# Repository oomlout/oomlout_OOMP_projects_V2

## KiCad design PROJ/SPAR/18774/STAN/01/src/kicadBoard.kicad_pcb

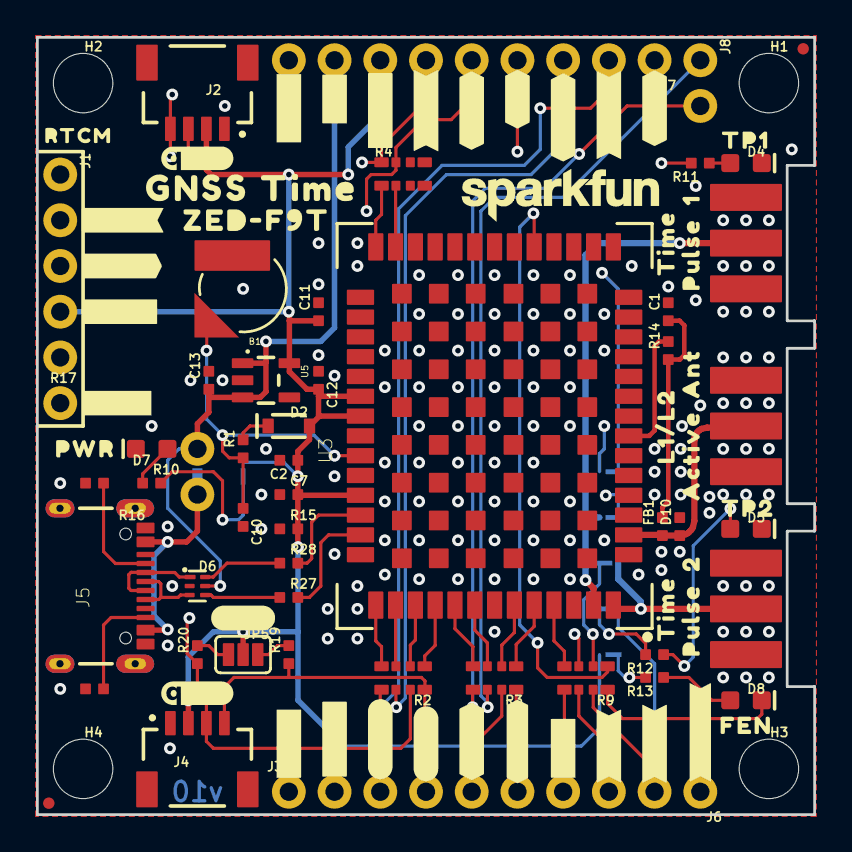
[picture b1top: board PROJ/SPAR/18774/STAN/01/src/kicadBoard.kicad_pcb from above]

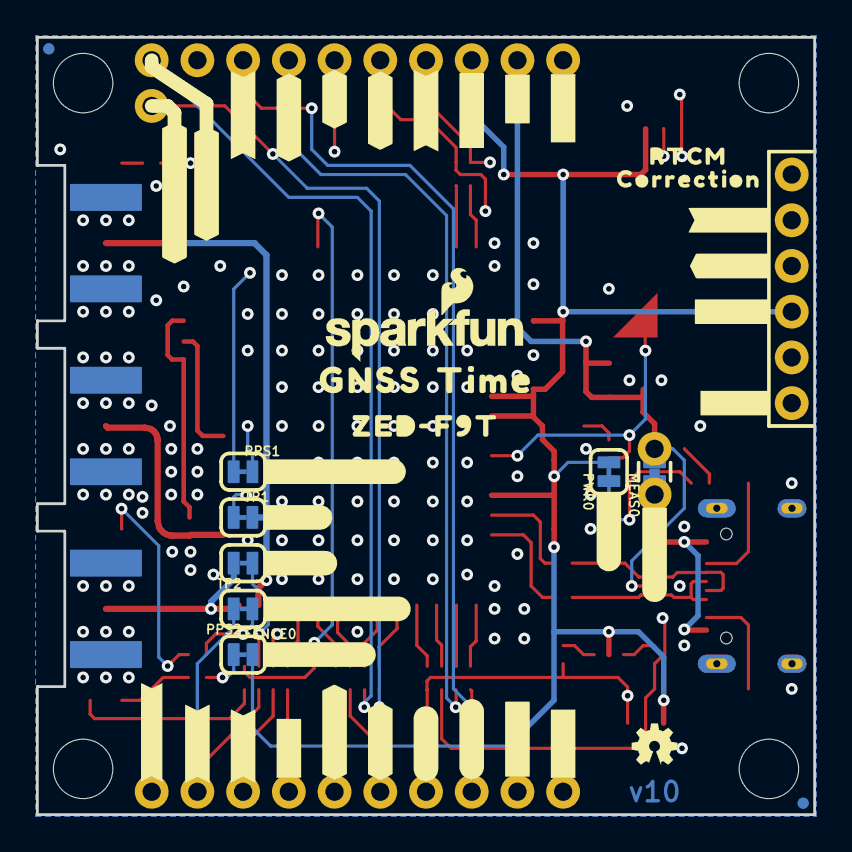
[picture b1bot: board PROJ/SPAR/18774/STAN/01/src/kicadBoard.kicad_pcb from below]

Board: 4 copper layers, 43.2 x 43.2 mm, 146 parts (47 on the bottom side), 57 nets.

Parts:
B1: 6.8MM_COIN_CELL; ML414H_IV01E
C1: 47pF; 0402-TIGHT
C2, C10, C11, C13: 1.0uF; 0402-TIGHT
C7, C12: 0.1uF; 0402-TIGHT
D2: 0.5A/40V/420mV; SOD-323
D4: YEL; LED-0603
D5: GRN; LED-0603
D6: PRTR5V0U2F; SOT886
D7: RED; LED-0603
D8: BLU; LED-0603
D10: PESD0402-0402T; 0402-TIGHT
E1, E2, E3: SMA; SMA-EDGE
FB1: 2.66Ω; 0402-TIGHT
FENCE0: JUMPER-SMT_2_NC_TRACE_SILK; SMT-JUMPER_2_NC_TRACE_SILK
FRAME2: FRAME-LEDGER; CREATIVE_COMMONS
H1, H2, H3, H4: STAND-OFF
J1: Radio; 1X06_NO_SILK
J2, J4: Qwiic Right Angle; JST04_1MM_RA
J3: PTH; 1X04_NO_SILK
J5: USB Female Type C Connector; USB-C-16P_4LAYER-PADS
J6: 1X06_NO_SILK
J7: 1X09_NO_SILK
J8: 1X02_NO_SILK
JP5: JUMPER-SMT_3_NO_SILK; SMT-JUMPER_3_NO_SILK
JP21, JP61, JP71, JP81: FIDUCIALUFIDUCIAL; FIDUCIAL-MICRO
LOGO1: OSHW-LOGOMINI; OSHW-LOGO-MINI
LOGO2: SFE_LOGO_NAME_FLAME.1_INCH; SFE_LOGO_NAME_FLAME_.1
LOGO3, LOGO4: QWIIC_LOGO_4MM; QWIIC_4MM
LOGO5: SFE_LOGO_NAME.1_INCH; SFE_LOGO_NAME_.1
MEAS0: JUMPER-COMBO_2_NC_TRACE; COMBO-JUMPER_2_NC_TRACE
PPS1, PPS2: JUMPER-SMT_2_NC_TRACE_SILK; SMT-JUMPER_2_NC_TRACE_SILK
PWR0: JUMPER-SMT_2_NC_TRACE_SILK; SMT-JUMPER_2_NC_TRACE_SILK
R1: 3.3K; 0402-TIGHT
R2, R3, R4, R9: 33; 1206_RA
R10, R11, R12, R13: 1k; 0402-TIGHT
R14: 10Ω; 0402-TIGHT
R15: 100k; 0402-TIGHT
R16, R17: 5.1k; 0402-TIGHT
R19, R20: 2.2k; 0402-TIGHT
R27, R28: 27OHM; 0402-TIGHT
TP1, TP2: JUMPER-SMT_2_NC_TRACE_SILK; SMT-JUMPER_2_NC_TRACE_SILK
U3: U-BLOX_ZED_F9T; ZED-F9X
U5: AP2112K-3.3V; SOT23-5
U$1, U$29, U$35, U$36, U$59, U$60: #3#3V#0
U$2: SPECIAL_INSTRUCTIONS-ORDERING; ORDERING_INSTRUCTIONS
U$3, U$28: #5V#1
U$4, U$27, U$38, U$39, U$61, U$62: #GND#2
U$5, U$8: ##CS##4
U$6: L1#L20
U$7, U$21: TIME0
U$9, U$10: #CIPO#6
U$11, U$12: #COPI#5
U$13: ACTIVE1
U$14, U$16: #RX2#1
U$15, U$37: ##RST##0
U$17, U$53: #SCL#3
U$18, U$22: #SDA#2
U$19, U$25: PULSE1
U$20: 12
U$23, U$24: #TX2#0
U$26: 20
U$30: #SCK#5
U$31: ANT1
U$32: #_TX2#0
U$33: #D_SEL#1
U$34, U$77: ZED#F9T0
U$40, U$70: GNSS0
U$41: ##SAFE##1
U$42, U$43: #INT#2
U$44, U$65: #FENCE#0
U$45: #TP2_LED#0
U$46, U$47: #TP1#3
U$48, U$49: #TP2#4
U$50: #TP2#0
U$51: #_FENCE#0
U$52: #TP1#0
U$54: #TP1_LED#0
U$55: #_RX2#0
U$56: PWR0
U$57: #PWR#0
U$58: #RX2_#0
U$63: TP10
U$64: TP21
U$66: #TX2_#0
U$67: #TX_RDY#0
U$68: #MEAS#0
U$69: #I�C#0
U$71, U$74: TIME1
U$72: ##SAFE##0
U$73: RTCM0
U$75: CORRECTION1
U$76: RTCM_0
U$78: FEN0

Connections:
3.3V: C2.1, C7.2, C11.1, C12.2, D2.A, FENCE0.2, J1.4, J2.2, J3.2, J4.2, J7.7, JP5.2, PWR0.2, R15.2, U3.33, U3.34, U3.38, U5.5
5V: C13.1, D6.5, J7.8, MEAS0.2, MEAS0.4, U5.1, U5.3
ANT_VCC: C1.1, FB1.2, R14.1
CC1: J5.A5, R17.2
CC2: J5.B5, R16.2
D+: D6.4, R27.1
D-: D6.6, R28.1
DSEL_LV: R3.P3, U3.47
D_SEL: J8.1, R3.P6
EXTINT: J6.4, R9.P5
EXTINT_LV: R9.P4, U3.51
FENCE_LV: R9.P1, U3.19
FENCE_STAT: D8.C, J6.1, R9.P8
GND: B1.-, C1.2, C2.2, C7.1, C10.2, C11.2, C12.1, C13.2, D4.C, D5.C, D6.2, D7.C, D10.2, E1.GND@0, E1.GND@1, E1.GND@2, E1.GND@3, E2.GND@0, E2.GND@1, E2.GND@2, E2.GND@3, E3.GND@0, E3.GND@1, E3.GND@2, E3.GND@3, J1.6, J2.1, J3.1, J4.1, J5.GND, J5.GND2, J7.9, R15.1, R16.1, R17.1, U3.1, U3.3, U3.12, U3.14, U3.32, U3.37, U3.41, U3.48, U3.G1, U3.G2, U3.G3, U3.G4, U3.G5, U3.G6, U3.G7, U3.G8, U3.G9, U3.G10, U3.G11, U3.G12, U3.G13, U3.G14, U3.G15, U3.G16, U3.G17, U3.G18, U3.G19, U3.G20, U3.G21, U3.G22, U3.G23, U3.G24, U3.G25, U3.G26, U3.G27, U3.G28, U3.G29, U3.G30, U3.G31, U3.G32, U3.G33, U3.G34, U3.G35, U3.G36, U3.G37, U3.G38, U3.G39, U3.G40, U3.G41, U3.G42, U3.G43, U3.G44, U3.G45, U3.G46, U3.G47, U3.G48, U5.2
GPS_ANT1: D10.1, E1.SIG, FB1.1, U3.2
unnamed: D4.A, R11.1
unnamed: PPS1.1, R11.2
unnamed: J5.VBUS1, J5.VBUS2, MEAS0.1, MEAS0.3
unnamed: R9.P3, TP1.1
unnamed: D2.C, R1.2
unnamed: R9.P2, TP2.1
unnamed: R27.2, U3.40
unnamed: R28.2, U3.39
unnamed: R14.2, U3.7
unnamed: D7.A, R10.1
unnamed: D5.A, R12.1
unnamed: PPS2.1, R12.2
unnamed: D8.A, R13.1
unnamed: FENCE0.1, R13.2
unnamed: PWR0.1, R10.2
unnamed: JP5.1, R20.2
unnamed: JP5.3, R19.2
PPS1_STAT: J6.3, PPS1.2, R9.P6
PPS2_STAT: J6.2, PPS2.2, R9.P7
RX1_LV: R2.P3, U3.43
RX2_LV: R4.P2, U3.26
RXI2: J1.3, J7.5, R4.P7
RXI/COPI: J7.3, R2.P6
SCL/SCK: J2.4, J3.4, J4.4, J7.1, R2.P8, R19.1
SCL_LV: R2.P1, U3.45
SDA/~CS: J2.3, J3.3, J4.3, J7.4, R2.P7, R20.1
SDA_LV: R2.P2, U3.44
TP1_LV: E2.SIG, TP1.2, U3.53
TP2_LV: E3.SIG, TP2.2, U3.54
TX1_LV: R2.P4, U3.42
TX2_LV: R4.P1, U3.27
TXO2: J1.2, J7.6, R4.P8
TXO/CIPO: J7.2, R2.P5
TX_READY: J8.2, R3.P5
TX_READY_LV: R3.P4, U3.46
UNP_D+: D6.3, J5.A6, J5.B6
UNP_D-: D6.1, J5.A7, J5.B7
V_BACKUP: B1.+, C10.1, R1.1, U3.36
~RESET: J6.6, R3.P7
~RESET_LV: R3.P2, U3.49
~SAFE: J6.5, R3.P8
~SAFE_LV: R3.P1, U3.50

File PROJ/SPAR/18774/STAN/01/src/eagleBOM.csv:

"Part";"Value";"Device";"Package";"Description";"DESIGNER";"PROD_ID";"REV";"VALUE";
"B1";"6.8MM_COIN_CELL";"ML414H_IV01E_BATTERY";"ML414H_IV01E";"SEIKO ML414H-IV01E Reflowable Lithium Battery";"";"BATT-14267";"";"";
"C1";"47pF";"47PF-0402_TIGHT-25V-5%-X7R";"0402-TIGHT";"47pF ceramic capacitors";"";"CAP-15063";"";"47pF";
"C2";"1.0uF";"1.0UF-0402T-16V-10%";"0402-TIGHT";"1µF ceramic capacitors";"";"CAP-12417";"";"1.0uF";
"C7";"0.1uF";"0.1UF-0402T-16V-10%";"0402-TIGHT";"0.1µF ceramic capacitors";"";"CAP-12416";"";"0.1uF";
"C10";"1.0uF";"1.0UF-0402T-16V-10%";"0402-TIGHT";"1µF ceramic capacitors";"";"CAP-12417";"";"1.0uF";
"C11";"1.0uF";"1.0UF-0402T-16V-10%";"0402-TIGHT";"1µF ceramic capacitors";"";"CAP-12417";"";"1.0uF";
"C12";"0.1uF";"0.1UF-0402T-6.3V-10%-X7R";"0402-TIGHT";"0.1µF ceramic capacitors";"";"CAP-14993";"";"0.1uF";
"C13";"1.0uF";"1.0UF-0402T-16V-10%";"0402-TIGHT";"1µF ceramic capacitors";"";"CAP-12417";"";"1.0uF";
"D2";"0.5A/40V/420mV";"DIODE-SCHOTTKY-PMEG4005EJ";"SOD-323";"Schottky diode";"";"DIO-10955";"";"0.5A/40V/420mV";
"D4";"YEL";"LED-YELLOW0603";"LED-0603";"Yellow SMD LED";"";"DIO-09003";"";"Yellow";
"D5";"GRN";"LED-GREEN0603";"LED-0603";"Green SMD LED";"";"DIO-00821";"";"GREEN";
"D6";"PRTR5V0U2F";"PRTR5V0U2F";"SOT886";"A small ESD protection device. Most commonly used on USB D+/D- signals to protect large, expensive, or especially sensitive USB enabled devices.";"";"DIO-14084";"";"";
"D7";"RED";"LED-RED0603";"LED-0603";"Red SMD LED";"";"DIO-00819";"";"RED";
"D8";"BLU";"LED-BLUE0603";"LED-0603";"Blue SMD LED";"";"DIO-08575";"";"BLUE";
"D10";"PESD0402-0402T";"PESD0402-0402T";"0402-TIGHT";"ESD protection diode";"";"DIO-15359";"";"";
"E1";"SMA";"ANTENNA-SMA-GROUNDEDEDGE_SMA";"SMA-EDGE";"SMA Antenna Connector w/ Ground";"";"CONN-08289";"";"";
"E2";"SMA";"ANTENNA-SMA-GROUNDEDEDGE_SMA";"SMA-EDGE";"SMA Antenna Connector w/ Ground";"";"CONN-08289";"";"";
"E3";"SMA";"ANTENNA-SMA-GROUNDEDEDGE_SMA";"SMA-EDGE";"SMA Antenna Connector w/ Ground";"";"CONN-08289";"";"";
"FB1";"2.66Ω";"FERRITE_BEAD-0402-2.66Ω-1GHZ";"0402-TIGHT";"Ferrite Bead (blocks, cores, rings, chokes, etc.)";"";"NDUC-15072";"";"2.66Ω";
"FENCE";"JUMPER-SMT_2_NC_TRACE_SILK";"JUMPER-SMT_2_NC_TRACE_SILK";"SMT-JUMPER_2_NC_TRACE_SILK";"Normally closed trace jumper";"";"";"";"";
"FRAME2";"FRAME-LEDGER";"FRAME-LEDGER";"CREATIVE_COMMONS";"Schematic Frame - Ledger";"";"";"";"";
"H1";"STAND-OFF";"STAND-OFF";"STAND-OFF";"Stand Off";"";"";"";"";
"H2";"STAND-OFF";"STAND-OFF";"STAND-OFF";"Stand Off";"";"";"";"";
"H3";"STAND-OFF";"STAND-OFF";"STAND-OFF";"Stand Off";"";"";"";"";
"H4";"STAND-OFF";"STAND-OFF";"STAND-OFF";"Stand Off";"";"";"";"";
"J1";"Radio";"6_PIN_SERIAL_TARGET_NO_SILK";"1X06_NO_SILK";"6-pin header connection for use with the "FTDI BASIC" pinout - TARGET SIDE.";"";"";"";"";
"J2";"Qwiic Right Angle";"I2C_STANDARDQWIIC";"JST04_1MM_RA";"SparkFun I2C Standard Pinout Header";"";"CONN-13694";"";"Qwiic Right Angle";
"J3";"PTH";"I2C_STANDARD_NO_SILK";"1X04_NO_SILK";"SparkFun I2C Standard Pinout Header";"";"";"";"";
"J4";"Qwiic Right Angle";"I2C_STANDARDQWIIC";"JST04_1MM_RA";"SparkFun I2C Standard Pinout Header";"";"CONN-13694";"";"Qwiic Right Angle";
"J5";"USB Female Type C Connector";"USB_C_4-LAYER_PADS";"USB-C-16P_4LAYER-PADS";"USB Type C 16Pin Connector";"";"CONN-14122";"";"";
"J6";"";"CONN_06NO_SILK_FEMALE_PTH";"1X06_NO_SILK";"Multi connection point. Often used as Generic Header-pin footprint for 0.1 inch spaced/style header connections";"";"CONN-08437";"";"";
"J7";"";"CONN_09NO_SILK";"1X09_NO_SILK";"Multi connection point. Often used as Generic Header-pin footprint for 0.1 inch spaced/style header connections";"";"";"";"";
"J8";"";"CONN_021X02_NO_SILK";"1X02_NO_SILK";"Multi connection point. Often used as Generic Header-pin footprint for 0.1 inch spaced/style header connections";"";"";"";"";
"JP5";"JUMPER-SMT_3_NO_SILK";"JUMPER-SMT_3_NO_SILK";"SMT-JUMPER_3_NO_SILK";"Normally open jumper";"";"";"";"";
"JP21";"FIDUCIALUFIDUCIAL";"FIDUCIALUFIDUCIAL";"FIDUCIAL-MICRO";"Fiducial Alignment Points";"";"";"";"";
"JP61";"FIDUCIALUFIDUCIAL";"FIDUCIALUFIDUCIAL";"FIDUCIAL-MICRO";"Fiducial Alignment Points";"";"";"";"";
"JP71";"FIDUCIALUFIDUCIAL";"FIDUCIALUFIDUCIAL";"FIDUCIAL-MICRO";"Fiducial Alignment Points";"";"";"";"";
"JP81";"FIDUCIALUFIDUCIAL";"FIDUCIALUFIDUCIAL";"FIDUCIAL-MICRO";"Fiducial Alignment Points";"";"";"";"";
"LOGO1";"OSHW-LOGOMINI";"OSHW-LOGOMINI";"OSHW-LOGO-MINI";"Open-Source Hardware (OSHW) Logo";"";"";"";"";
"LOGO2";"SFE_LOGO_NAME_FLAME.1_INCH";"SFE_LOGO_NAME_FLAME.1_INCH";"SFE_LOGO_NAME_FLAME_.1";"SparkFun Font Logo w/ Flame";"";"";"";"";
"LOGO4";"QWIIC_LOGO_4MM";"QWIIC_LOGO_4MM";"QWIIC_4MM";"Qwiic Logos for placement on schematic and PCB. The 5.5mm silk logo is best for placing next to Qwiic connector.";"";"";"";"";
"LOGO5";"SFE_LOGO_NAME.1_INCH";"SFE_LOGO_NAME.1_INCH";"SFE_LOGO_NAME_.1";"SparkFun Font Logo";"";"";"";"";
"MEAS";"JUMPER-COMBO_2_NC_TRACE";"JUMPER-COMBO_2_NC_TRACE";"COMBO-JUMPER_2_NC_TRACE";"";"";"";"";"";
"PPS1";"JUMPER-SMT_2_NC_TRACE_SILK";"JUMPER-SMT_2_NC_TRACE_SILK";"SMT-JUMPER_2_NC_TRACE_SILK";"Normally closed trace jumper";"";"";"";"";
"PPS2";"JUMPER-SMT_2_NC_TRACE_SILK";"JUMPER-SMT_2_NC_TRACE_SILK";"SMT-JUMPER_2_NC_TRACE_SILK";"Normally closed trace jumper";"";"";"";"";
"PWR";"JUMPER-SMT_2_NC_TRACE_SILK";"JUMPER-SMT_2_NC_TRACE_SILK";"SMT-JUMPER_2_NC_TRACE_SILK";"Normally closed trace jumper";"";"";"";"";
"R1";"3.3K";"3.3KOHM-0402T-1/16W-1%";"0402-TIGHT";"3.3kΩ resistor";"";"RES-15923";"";"";
"R2";"33";"33OHM_RA-1206-1/16W-5%";"1206_RA";"EXB-38V330JV";"";"RES-15081";"";"33";
"R3";"33";"33OHM_RA-1206-1/16W-5%";"1206_RA";"EXB-38V330JV";"";"RES-15081";"";"33";
"R4";"33";"33OHM_RA-1206-1/16W-5%";"1206_RA";"EXB-38V330JV";"";"RES-15081";"";"33";
"R9";"33";"33OHM_RA-1206-1/16W-5%";"1206_RA";"EXB-38V330JV";"";"RES-15081";"";"33";
"R10";"1k";"1KOHM-0402T-1/16W-1%";"0402-TIGHT";"1kΩ resistor";"";"RES-14342";"";"1k";
"R11";"1k";"1KOHM-0402T-1/16W-1%";"0402-TIGHT";"1kΩ resistor";"";"RES-14342";"";"1k";
"R12";"1k";"1KOHM-0402T-1/16W-1%";"0402-TIGHT";"1kΩ resistor";"";"RES-14342";"";"1k";
"R13";"1k";"1KOHM-0402T-1/16W-1%";"0402-TIGHT";"1kΩ resistor";"";"RES-14342";"";"1k";
"R14";"10Ω";"10OHM-0402-1/16W-5%";"0402-TIGHT";"10Ω resistor";"";"RES-16072";"";"10Ω";
"R15";"100k";"100KOHM-0402T-1/16W-1%";"0402-TIGHT";"100kΩ resistor";"";"RES-13495";"";"100k";
"R16";"5.1k";"5.1KOHM-0402T-1/16W-1%";"0402-TIGHT";"";"";"RES-14340";"";"5.1k";
"R17";"5.1k";"5.1KOHM-0402T-1/16W-1%";"0402-TIGHT";"";"";"RES-14340";"";"5.1k";
"R19";"2.2k";"2.2KOHM-0402T-1/16W-1%";"0402-TIGHT";"2.2kΩ resistor";"";"RES-14341";"";"2.2k";
"R20";"2.2k";"2.2KOHM-0402T-1/16W-1%";"0402-TIGHT";"2.2kΩ resistor";"";"RES-14341";"";"2.2k";
"R27";"27OHM";"27OHM";"0402-TIGHT";"27Ω resistor";"";"RES-15238";"";"";
"R28";"27OHM";"27OHM";"0402-TIGHT";"27Ω resistor";"";"RES-15238";"";"";
"TP1";"JUMPER-SMT_2_NC_TRACE_SILK";"JUMPER-SMT_2_NC_TRACE_SILK";"SMT-JUMPER_2_NC_TRACE_SILK";"Normally closed trace jumper";"";"";"";"";
"TP2";"JUMPER-SMT_2_NC_TRACE_SILK";"JUMPER-SMT_2_NC_TRACE_SILK";"SMT-JUMPER_2_NC_TRACE_SILK";"Normally closed trace jumper";"";"";"";"";
"U$2";"SPECIAL_INSTRUCTIONS-ORDERING";"SPECIAL_INSTRUCTIONS-ORDERING";"ORDERING_INSTRUCTIONS";"Special Ordering/Production Instructions Alert";"";"";"";"";
"U3";"U-BLOX_ZED_F9T";"U-BLOX_ZED_F9RT";"ZED-F9X";"u-blox ZED-F9T";"";"IC-16292";"";"";
"U5";"AP2112K-3.3V";"V_REG_AP2112K-3.3V";"SOT23-5";"AP2112 - 600mA CMOS LDO Regulator w/ Enable";"";"VREG-12457";"";"3.3V";

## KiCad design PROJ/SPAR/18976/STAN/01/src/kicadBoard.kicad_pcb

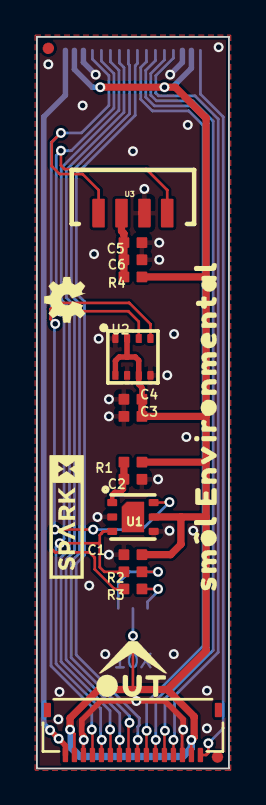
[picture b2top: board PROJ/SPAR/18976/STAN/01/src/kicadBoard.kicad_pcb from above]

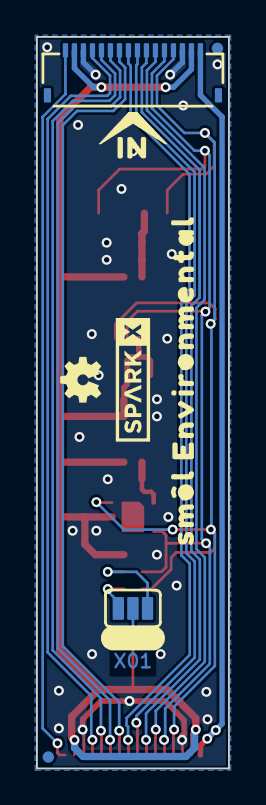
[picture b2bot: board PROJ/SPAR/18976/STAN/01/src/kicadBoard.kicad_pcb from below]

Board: 2 copper layers, 10.7 x 40.6 mm, 33 parts (10 on the bottom side), 18 nets.

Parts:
C1, C2: 1.0uF; 0402-TIGHT
C3, C5: 2.2uF; 0402-TIGHT
C4, C6: 0.1uF; 0402-TIGHT
FD1, FD2, FD3, FD4: FIDUCIALUFIDUCIAL; FIDUCIAL-MICRO
FRAME1: FRAME-LEDGER; CREATIVE_COMMONS
IN0: FPC_16_0.5MM
JP1: JUMPER-SMT_3_NO_SILK; SMT-JUMPER_3_NO_SILK
LOGO1: SPECIAL_INSTRUCTIONS-ORDERING; ORDERING_INSTRUCTIONS
LOGO2, LOGO3: OSHW-LOGOMINI; OSHW-LOGO-MINI
OUT0: FPC_16_0.5MM
R1, R4: 4.7; 0402-TIGHT
R2, R3: 4.7k; 0402-TIGHT
U1: SGP40
U2: BME280; LGA-8-2.5X2.5
U3: VEML7700-TT; VEML7700_TT
U$1, U$20: SPARKX-LOGO3; SPARKX-SMALL
U$2, U$4: SM�L_ENVIRONMENTAL0
U$3, U$9: SMOL_LOGOSMALL; SMOL_SMALL
U$5: #I�C#0
U$8: IN0
U$17: OUT0

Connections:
3.3V: C1.1, C3.1, C4.1, IN0.2, IN0.15, JP1.2, OUT0.2, OUT0.15, R1.2, R4.2, U1.5, U2.2, U2.6, U2.8
CIPO: IN0.6, OUT0.6
COPI: IN0.5, OUT0.5
CS0: IN0.7, OUT0.7
CS1: IN0.8, OUT0.8
CS2: IN0.9, OUT0.9
GND: C1.2, C2.2, C3.2, C4.2, C5.2, C6.2, IN0.3, IN0.14, OUT0.3, OUT0.14, U1.2, U1.4, U1.DIEPAD, U2.1, U2.5, U2.7, U3.3
GPIO0: IN0.10, OUT0.10
GPIO1: IN0.11, OUT0.11
unnamed: C2.1, R1.1, U1.1
unnamed: JP1.3, R2.2
unnamed: JP1.1, R3.2
unnamed: C5.1, C6.1, R4.1, U3.2
PROC_PWR_EN: IN0.1, OUT0.1
SCL: IN0.13, OUT0.13, R3.1, U1.6, U2.4, U3.1
SCLK: IN0.4, OUT0.4
SDA: IN0.12, OUT0.12, R2.1, U1.3, U2.3, U3.4
V_USB: IN0.16, OUT0.16

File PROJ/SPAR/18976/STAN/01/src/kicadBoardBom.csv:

"Id";"Designator";"Package";"Quantity";"Designation";"Supplier and ref";
1;"R1,R4";"0402-TIGHT";2;"4.7";;;
2;"R3,R2";"0402-TIGHT";2;"4.7k";;;
3;"C6,C4";"0402-TIGHT";2;"0.1uF";;;
4;"FD1,FD3,FD2,FD4";"FIDUCIAL-MICRO";4;"FIDUCIALUFIDUCIAL";;;
5;"U2";"LGA-8-2.5X2.5";1;"BME280";;;
6;"U$2,U$4";"SM�L_ENVIRONMENTAL0";2;"";;;
7;"U3";"VEML7700_TT";1;"VEML7700-TT";;;
8;"OUT0,IN0";"FPC_16_0.5MM";2;"";;;
9;"U$3,U$9";"SMOL_SMALL";2;"SMOL_LOGOSMALL";;;
10;"LOGO2,LOGO3";"OSHW-LOGO-MINI";2;"OSHW-LOGOMINI";;;
11;"U$1,U$20";"SPARKX-SMALL";2;"SPARKX-LOGO3";;;
12;"C3,C5";"0402-TIGHT";2;"2.2uF";;;
13;"C1,C2";"0402-TIGHT";2;"1.0uF";;;
14;"U1";"SGP40";1;"SGP40";;;
15;"LOGO1";"ORDERING_INSTRUCTIONS";1;"SPECIAL_INSTRUCTIONS-ORDERING";;;
16;"U$17";"OUT0";1;"";;;
17;"FRAME1";"CREATIVE_COMMONS";1;"FRAME-LEDGER";;;
18;"U$5";"#I�C#0";1;"";;;
19;"U$8";"IN0";1;"";;;
20;"JP1";"SMT-JUMPER_3_NO_SILK";1;"JUMPER-SMT_3_NO_SILK";;;

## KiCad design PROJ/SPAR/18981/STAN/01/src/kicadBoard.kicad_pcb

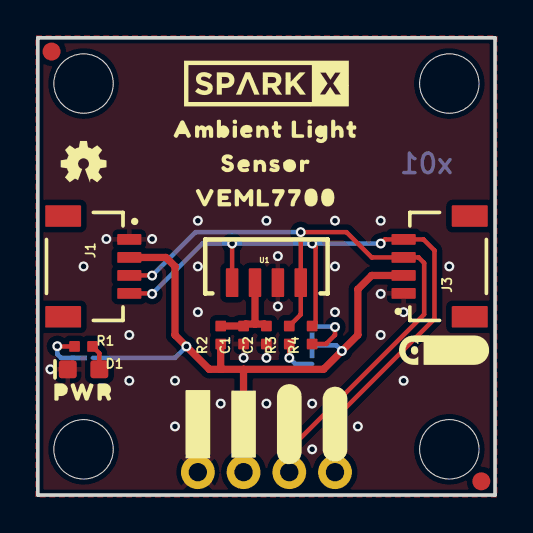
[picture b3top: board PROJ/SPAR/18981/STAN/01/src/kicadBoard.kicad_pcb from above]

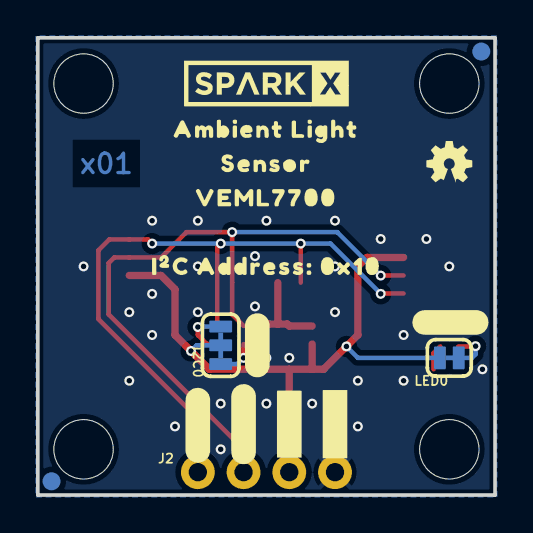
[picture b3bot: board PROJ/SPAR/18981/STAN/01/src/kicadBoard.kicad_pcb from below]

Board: 2 copper layers, 25.4 x 25.4 mm, 46 parts (17 on the bottom side), 9 nets.

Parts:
C1: 2.2uF; 0402-TIGHT
C2: 0.1uF; 0402-TIGHT
D1: RED; LED-0603
FRAME1: FRAME-LETTER; CREATIVE_COMMONS
I2C0: JUMPER-SMT_3_2-NC_TRACE_SILK; SMT-JUMPER_3_2-NC_TRACE_SILK
J1, J3: Qwiic Right Angle; JST04_1MM_RA
J2: PTH; 1X04_NO_SILK
JP1, JP2, JP5, JP6: FIDUCIAL1X2; FIDUCIAL-1X2
JP3, JP4, JP7, JP8: STAND-OFF
LED0: SMT-JUMPER_2_NC_TRACE_SILK
LOGO1, LOGO4: OSHW-LOGOMINI; OSHW-LOGO-MINI
LOGO2: SPECIAL_INSTRUCTIONS-ORDERING; ORDERING_INSTRUCTIONS
LOGO3: QWIIC_LOGO_5MM; QWIIC_5MM
R1: 1k; 0402-TIGHT
R2: 4.7; 0402-TIGHT
R3, R4: 4.7k; 0402-TIGHT
U1: VEML7700-TT; VEML7700_TT
U$1, U$3: #3V3#0
U$2, U$21: SPARKX-LOGO4; SPARKX-MEDIUM
U$4, U$5: #GND#0
U$6, U$7: #SDA#0
U$8, U$9: #SCL#0
U$10: PWR0
U$11, U$12: AMBIENT_LIGHT0
U$13, U$14: SENSOR0
U$15, U$16: VEML77000
U$17: #I�C#0
U$18: I�C_ADDRESS#_0X100
U$19: #LED#0

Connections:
3.3V: I2C0.2, J1.2, J2.2, J3.2, LED0.2, R2.2
GND: C1.2, C2.2, D1.C, J1.1, J2.1, J3.1, U1.3
unnamed: I2C0.1, R4.2
unnamed: I2C0.3, R3.2
unnamed: D1.A, R1.1
unnamed: LED0.1, R1.2
unnamed: C1.1, C2.1, R2.1, U1.2
SCL: J1.4, J2.4, J3.4, R4.1, U1.1
SDA: J1.3, J2.3, J3.3, R3.1, U1.4

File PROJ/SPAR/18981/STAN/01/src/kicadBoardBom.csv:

"Id";"Designator";"Package";"Quantity";"Designation";"Supplier and ref";
1;"LOGO3";"QWIIC_5MM";1;"QWIIC_LOGO_5MM";;;
2;"U$15,U$16";"VEML77000";2;"";;;
3;"FRAME1";"CREATIVE_COMMONS";1;"FRAME-LETTER";;;
4;"R3,R4";"0402-TIGHT";2;"4.7k";;;
5;"D1";"LED-0603";1;"RED";;;
6;"U$6,U$7";"#SDA#0";2;"";;;
7;"U$21,U$2";"SPARKX-MEDIUM";2;"SPARKX-LOGO4";;;
8;"JP6,JP2,JP5,JP1";"FIDUCIAL-1X2";4;"FIDUCIAL1X2";;;
9;"JP3,JP8,JP7,JP4";"STAND-OFF";4;"STAND-OFF";;;
10;"C1";"0402-TIGHT";1;"2.2uF";;;
11;"U$11,U$12";"AMBIENT_LIGHT0";2;"";;;
12;"R1";"0402-TIGHT";1;"1k";;;
13;"U$8,U$9";"#SCL#0";2;"";;;
14;"R2";"0402-TIGHT";1;"4.7";;;
15;"J3,J1";"JST04_1MM_RA";2;"Qwiic Right Angle";;;
16;"C2";"0402-TIGHT";1;"0.1uF";;;
17;"LOGO1,LOGO4";"OSHW-LOGO-MINI";2;"OSHW-LOGOMINI";;;
18;"LOGO2";"ORDERING_INSTRUCTIONS";1;"SPECIAL_INSTRUCTIONS-ORDERING";;;
19;"U$1,U$3";"#3V3#0";2;"";;;
20;"U$13,U$14";"SENSOR0";2;"";;;
21;"U$4,U$5";"#GND#0";2;"";;;
22;"U$10";"PWR0";1;"";;;
23;"U1";"VEML7700_TT";1;"VEML7700-TT";;;
24;"J2";"1X04_NO_SILK";1;"PTH";;;
25;"U$18";"I�C_ADDRESS#_0X100";1;"";;;
26;"U$19";"#LED#0";1;"";;;
27;"U$17";"#I�C#0";1;"";;;
28;"LED0";"SMT-JUMPER_2_NC_TRACE_SILK";1;"";;;
29;"I2C0";"SMT-JUMPER_3_2-NC_TRACE_SILK";1;"JUMPER-SMT_3_2-NC_TRACE_SILK";;;

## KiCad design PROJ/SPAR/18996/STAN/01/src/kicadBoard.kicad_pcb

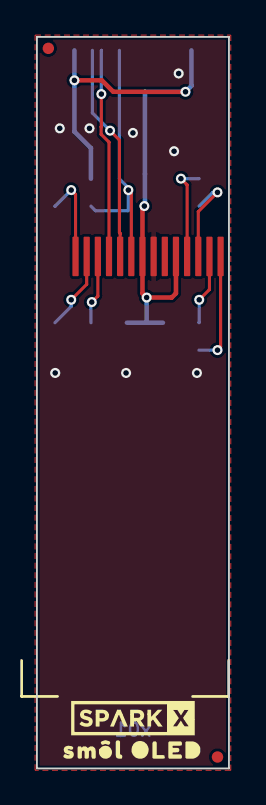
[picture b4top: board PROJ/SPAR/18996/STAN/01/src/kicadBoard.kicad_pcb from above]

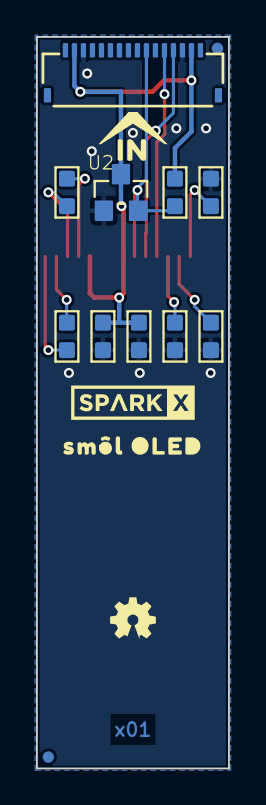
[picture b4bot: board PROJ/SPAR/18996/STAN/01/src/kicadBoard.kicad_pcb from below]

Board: 2 copper layers, 10.7 x 40.6 mm, 24 parts (17 on the bottom side), 12 nets.

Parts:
C1, C2: 1uF ±10% 16V; 0603
C3: 4.7uF ±10% 6.3V; 0603
C4: 0.1uF ±10% 25V; 0603
C5: 2.2uF ±10% 16V; 0603
C6: 4.7uF ±10% 16V; 0603
D1: OLED-12832
FD1, FD2, FD3, FD4: FIDUCIALUFIDUCIAL; FIDUCIAL-MICRO
FRAME1: FRAME-LEDGER; CREATIVE_COMMONS
IN0: FPC_16_0.5MM
LOGO1: SPECIAL_INSTRUCTIONS-ORDERING; ORDERING_INSTRUCTIONS
LOGO3: OSHW-LOGOMINI; OSHW-LOGO-MINI
R3: 560K 10%; 0603
R4: 10K ±5%; 0603
U2: APX803; SOT23
U$1, U$4: SM�L_OLED0
U$3, U$20: SPARKX-LOGO3; SPARKX-SMALL
U$12: IN0
U$14: SMOL_LOGOSMALL; SMOL_SMALL

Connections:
3.3V: C3.1, C4.1, D1.5, D1.8, IN0.2, IN0.15, R4.2, U2.3
GND: C3.2, C4.2, C5.2, C6.2, D1.7, IN0.3, IN0.14, R3.1, U2.1
GPIO0: D1.9, IN0.10, R4.1, U2.2
unnamed: C1.2, D1.1
unnamed: C1.1, D1.2
unnamed: C2.2, D1.3
unnamed: C2.1, D1.4
unnamed: C5.1, D1.13
unnamed: C6.1, D1.14
unnamed: D1.12, R3.2
SCL: D1.10, IN0.13
SDA: D1.11, IN0.12

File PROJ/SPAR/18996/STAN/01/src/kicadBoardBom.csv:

"Id";"Designator";"Package";"Quantity";"Designation";"Supplier and ref";
1;"U$3,U$20";"SPARKX-SMALL";2;"SPARKX-LOGO3";;;
2;"LOGO1";"ORDERING_INSTRUCTIONS";1;"SPECIAL_INSTRUCTIONS-ORDERING";;;
3;"FD3,FD1,FD4,FD2";"FIDUCIAL-MICRO";4;"FIDUCIALUFIDUCIAL";;;
4;"U$4,U$1";"SM�L_OLED0";2;"";;;
5;"D1";"OLED-12832";1;"OLED-12832";;;
6;"FRAME1";"CREATIVE_COMMONS";1;"FRAME-LEDGER";;;
7;"LOGO3";"OSHW-LOGO-MINI";1;"OSHW-LOGOMINI";;;
8;"U2";"SOT23";1;"APX803";;;
9;"R4";"0603";1;"10K ±5%";;;
10;"R3";"0603";1;"560K 10%";;;
11;"C5";"0603";1;"2.2uF ±10% 16V";;;
12;"C1,C2";"0603";2;"1uF ±10% 16V ";;;
13;"C4";"0603";1;"0.1uF ±10% 25V";;;
14;"C6";"0603";1;"4.7uF ±10% 16V";;;
15;"IN0";"FPC_16_0.5MM";1;"";;;
16;"C3";"0603";1;"4.7uF ±10% 6.3V";;;
17;"U$12";"IN0";1;"";;;
18;"U$14";"SMOL_SMALL";1;"SMOL_LOGOSMALL";;;

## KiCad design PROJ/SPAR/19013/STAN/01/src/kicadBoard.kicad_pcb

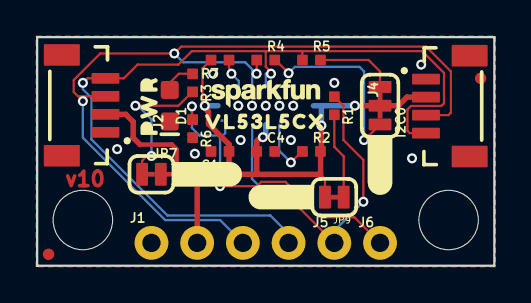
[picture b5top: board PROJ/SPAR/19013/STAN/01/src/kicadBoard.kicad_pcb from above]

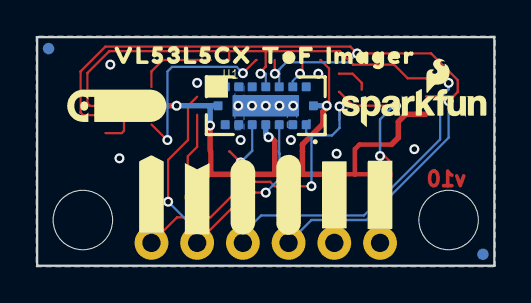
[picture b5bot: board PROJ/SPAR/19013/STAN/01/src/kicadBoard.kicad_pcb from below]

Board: 2 copper layers, 25.4 x 12.7 mm, 45 parts (14 on the bottom side), 13 nets.

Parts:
C1: 4.7uF; 0402-TIGHT
C4: 0.1uF; 0402-TIGHT
D1: RED; LED-0603
FRAME1: FRAME-LETTER; CREATIVE_COMMONS
I2C0: JUMPER-SMT_3_2-NC_TRACE_SILK; SMT-JUMPER_3_2-NC_TRACE_SILK
J1: 1X04_NO_SILK
J2, J4: Vertical Qwiic Connector; JST04_1MM_VERT
J5, J6: 1X01_NO_SILK
JP1, JP2, JP5, JP6: FIDUCIALUFIDUCIAL; FIDUCIAL-MICRO
JP7: PWR_LED; SMT-JUMPER_2_NC_TRACE_SILK
JP9: INT; SMT-JUMPER_2_NC_TRACE_SILK
JP10, JP11: STAND-OFF
LOGO1: SFE_LOGO_NAME_FLAME8_MM; SFE_LOGO_NAME_FLAME_8MM
LOGO2: OSHW-LOGONO_SILK; DUMMY
LOGO3: QWIIC_LOGO_CONNECTOR; QWIIC_5.5MM
LOGO4: SFE_LOGO_NAME6_MM; SFE_LOGO_NAME_6MM
LOGO5: SPECIAL_INSTRUCTIONS-ORDERING; ORDERING_INSTRUCTIONS
R1, R2, R6, R7: 47k; 0402-TIGHT
R3: 1k; 0402-TIGHT
R4, R5: 2.2k; 0402-TIGHT
U1: VL53L5CX
U$1: VL53L5CX_0
U$2: #LED#0
U$3: #3V3#13
U$4: PWR12
U$5: #INT#0
U$8: #INT_#0
U$9: #RST_#1
U$16: #I�C#0
U$19: VL53L5CX0
U$20: TOF1
U$22: IMAGER2
U$24: #SCL#1
U$25: #SDA#0
U$30: #GND#62130

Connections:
3.3V: C1.1, C4.1, I2C0.2, J1.2, J2.2, J4.2, JP7.2, JP9.2, R2.2, R7.2, U1.A4, U1.B1, U1.B7
GND: C1.2, C4.2, D1.C, J1.1, J2.1, J4.1, R6.2, U1.A2, U1.A6, U1.A7, U1.B4, U1.C1, U1.C6, U1.C7
INT: J5.1, R1.1, U1.A3
unnamed: I2C0.1, R5.2
unnamed: I2C0.3, R4.2
unnamed: D1.A, R3.1
unnamed: JP9.1, R1.2
unnamed: JP7.1, R3.2
unnamed: R7.1, U1.C2
RST: J6.1, R6.1, U1.A1
SCL: J1.4, J2.4, J4.4, R5.1, U1.C4
SDA: J1.3, J2.3, J4.3, R4.1, U1.C3
~LP: R2.1, U1.A5

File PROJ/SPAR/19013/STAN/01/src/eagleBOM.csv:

"Part";"Value";"Device";"Package";"Description";"DESIGNER";"PROD_ID";"REV";"VALUE";
"C1";"4.7uF";"4.7UF-0402_TIGHT-6.3V-20%-X5R";"0402-TIGHT";"4.7µF ceramic capacitors";"";"CAP-14240";"";"4.7uF";
"C4";"0.1uF";"0.1UF-0402T-6.3V-10%-X7R";"0402-TIGHT";"0.1µF ceramic capacitors";"";"CAP-14993";"";"0.1uF";
"D1";"RED";"LED-RED0603";"LED-0603";"Red SMD LED";"";"DIO-00819";"";"RED";
"FRAME1";"FRAME-LETTER";"FRAME-LETTER";"CREATIVE_COMMONS";"Schematic Frame - Letter";"";"";"";"";
"I2C";"JUMPER-SMT_3_2-NC_TRACE_SILK";"JUMPER-SMT_3_2-NC_TRACE_SILK";"SMT-JUMPER_3_2-NC_TRACE_SILK";"Normally closed trace jumper (2 of 2 connections)";"";"";"";"";
"J1";"";"CONN_041X04_NO_SILK";"1X04_NO_SILK";"Multi connection point. Often used as Generic Header-pin footprint for 0.1 inch spaced/style header connections";"";"CONN-09696";"";"";
"J2";"Vertical Qwiic Connector";"QWIIC_CONNECTOR";"JST04_1MM_VERT";"SparkFun I2C Standard Qwiic Connector";"";"CONN-14483";"";"Vertical Qwiic Connector";
"J4";"Vertical Qwiic Connector";"QWIIC_CONNECTOR";"JST04_1MM_VERT";"SparkFun I2C Standard Qwiic Connector";"";"CONN-14483";"";"Vertical Qwiic Connector";
"J5";"";"CONN_01PTH_NO_SILK_YES_STOP";"1X01_NO_SILK";"Single connection point. Often used as Generic Header-pin footprint for 0.1 inch spaced/style header connections";"";"";"";"";
"J6";"";"CONN_01PTH_NO_SILK_YES_STOP";"1X01_NO_SILK";"Single connection point. Often used as Generic Header-pin footprint for 0.1 inch spaced/style header connections";"";"";"";"";
"JP1";"FIDUCIALUFIDUCIAL";"FIDUCIALUFIDUCIAL";"FIDUCIAL-MICRO";"Fiducial Alignment Points";"";"";"";"";
"JP2";"FIDUCIALUFIDUCIAL";"FIDUCIALUFIDUCIAL";"FIDUCIAL-MICRO";"Fiducial Alignment Points";"";"";"";"";
"JP5";"FIDUCIALUFIDUCIAL";"FIDUCIALUFIDUCIAL";"FIDUCIAL-MICRO";"Fiducial Alignment Points";"";"";"";"";
"JP6";"FIDUCIALUFIDUCIAL";"FIDUCIALUFIDUCIAL";"FIDUCIAL-MICRO";"Fiducial Alignment Points";"";"";"";"";
"JP7";"PWR_LED";"JUMPER-SMT_2_NC_TRACE_SILK";"SMT-JUMPER_2_NC_TRACE_SILK";"Normally closed trace jumper";"";"";"";"";
"JP9";"INT";"JUMPER-SMT_2_NC_TRACE_SILK";"SMT-JUMPER_2_NC_TRACE_SILK";"Normally closed trace jumper";"";"";"";"";
"JP10";"STAND-OFF";"STAND-OFF";"STAND-OFF";"Stand Off";"";"";"";"";
"JP11";"STAND-OFF";"STAND-OFF";"STAND-OFF";"Stand Off";"";"";"";"";
"LOGO1";"SFE_LOGO_NAME_FLAME8_MM";"SFE_LOGO_NAME_FLAME8_MM";"SFE_LOGO_NAME_FLAME_8MM";"SparkFun Font Logo w/ Flame";"";"";"";"";
"LOGO2";"OSHW-LOGONO_SILK";"OSHW-LOGONO_SILK";"DUMMY";"Open-Source Hardware (OSHW) Logo";"";"";"";"";
"LOGO3";"QWIIC_LOGO_CONNECTOR";"QWIIC_LOGO_CONNECTOR";"QWIIC_5.5MM";"Qwiic Logos for placement on schematic and PCB. The 5.5mm silk logo is best for placing next to Qwiic connector.";"";"";"";"";
"LOGO4";"SFE_LOGO_NAME6_MM";"SFE_LOGO_NAME6_MM";"SFE_LOGO_NAME_6MM";"SparkFun Font Logo";"";"";"";"";
"LOGO5";"SPECIAL_INSTRUCTIONS-ORDERING";"SPECIAL_INSTRUCTIONS-ORDERING";"ORDERING_INSTRUCTIONS";"Special Ordering/Production Instructions Alert";"";"";"";"";
"R1";"47k";"47KOHM-0402-1/10W-1%";"0402-TIGHT";"47kΩ resistor";"";"RES-15011";"";"47k";
"R2";"47k";"47KOHM-0402-1/10W-1%";"0402-TIGHT";"47kΩ resistor";"";"RES-15011";"";"47k";
"R3";"1k";"1KOHM-0402T-1/16W-1%";"0402-TIGHT";"1kΩ resistor";"";"RES-14342";"";"1k";
"R4";"2.2k";"2.2KOHM-0402T-1/16W-1%";"0402-TIGHT";"2.2kΩ resistor";"";"RES-14341";"";"2.2k";
"R5";"2.2k";"2.2KOHM-0402T-1/16W-1%";"0402-TIGHT";"2.2kΩ resistor";"";"RES-14341";"";"2.2k";
"R6";"47k";"47KOHM-0402-1/10W-1%";"0402-TIGHT";"47kΩ resistor";"";"RES-15011";"";"47k";
"R7";"47k";"47KOHM-0402-1/10W-1%";"0402-TIGHT";"47kΩ resistor";"";"RES-15011";"";"47k";
"U1";"VL53L5CX";"VL53L5CX";"VL53L5CX";"";"";"IC-16254";"";"";

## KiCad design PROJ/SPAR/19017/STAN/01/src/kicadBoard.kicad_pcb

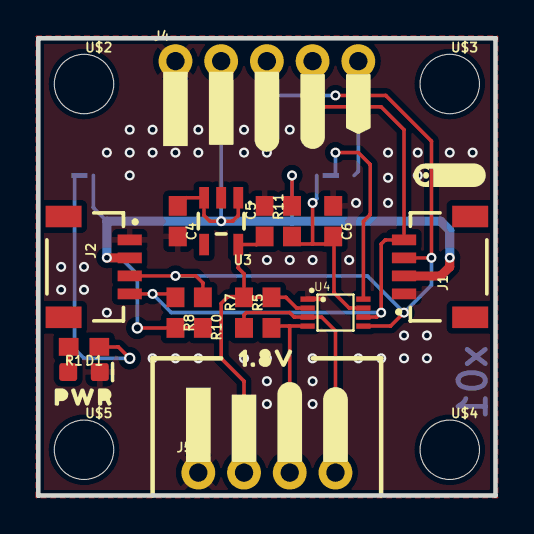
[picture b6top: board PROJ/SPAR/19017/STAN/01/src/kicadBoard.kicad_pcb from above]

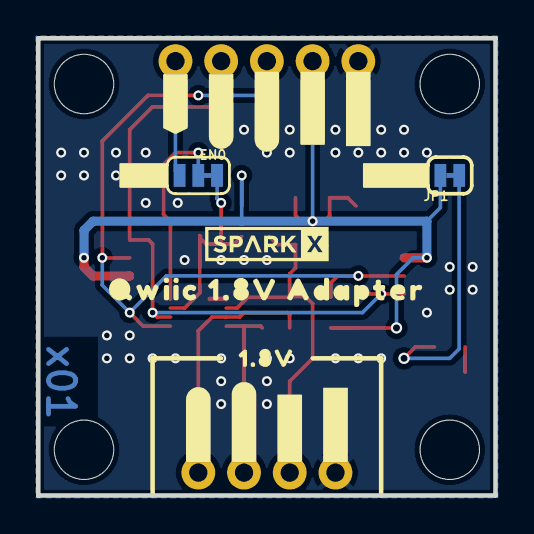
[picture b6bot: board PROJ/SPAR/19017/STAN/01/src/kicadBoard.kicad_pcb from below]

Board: 2 copper layers, 25.4 x 25.4 mm, 49 parts (16 on the bottom side), 12 nets.

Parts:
C4, C5: 1.0uF; 0603
C6: 100pF; 0603
D1: RED; LED-0603
EN0: JUMPER-SMT_3_1-NC_TRACE_SILK; SMT-JUMPER_3_1-NC_TRACE_SILK
FRAME1: FRAME-LETTER; CREATIVE_COMMONS
J1, J2: QWIIC_RIGHT_ANGLE; JST04_1MM_RA
J4: 1X05_NO_SILK
J5: 1X04_NO_SILK
JP1: JUMPER-SMT_2_NC_TRACE_SILK; SMT-JUMPER_2_NC_TRACE_SILK
R1: 1k; 0603
R5, R7, R8, R10: 2.2k; 0603
R11: 200k; 0603
U3: AP2127K-1.8V; SOT23-5
U4: VSSOP_8PIN
U$1, U$17: #_GND#0
U$2, U$3, U$4, U$5: STAND-OFF
U$6, U$18: #_1V8#0
U$7, U$19: #_SDA#0
U$8, U$20: #_SCL#0
U$9: PWR0
U$10, U$21: #GND_#0
U$11, U$22: #3V3_#0
U$12, U$23: #SDA_#0
U$13, U$24: #SCL_#0
U$14, U$25: #EN_#0
U$15, U$26: 1#8V0
U$16: QWIIC_4MM
U$27: #EN#0
U$28: QWIIC_1#8V_ADAPTER0
U$29: SPARKX-SMALL
U$30: #LED#0

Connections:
1.8V: C5.1, J5.2, R5.2, R7.2, U3.5, U4.P2
3.3V: C4.1, J1.2, J2.2, J4.2, JP1.2, R8.2, R10.2, R11.2, U3.1, U3.3
EN: EN0.1, J4.5
GND: C4.2, C5.2, C6.1, D1.C, J1.1, J2.1, J4.1, J5.1, U3.2, U4.P1
unnamed: EN0.2, U4.P8
unnamed: D1.A, R1.2
unnamed: JP1.1, R1.1
unnamed: C6.2, EN0.3, R11.1, U4.P7
SCL1_8: J5.4, R7.1, U4.P3
SCL3_3: J1.4, J2.4, J4.4, R8.1, U4.P6
SDA1_8: J5.3, R5.1, U4.P4
SDA3_3: J1.3, J2.3, J4.3, R10.1, U4.P5

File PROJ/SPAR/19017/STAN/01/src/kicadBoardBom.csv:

"Id";"Designator";"Package";"Quantity";"Designation";"Supplier and ref";
1;"C5,C4";"0603";2;"1.0uF";;;
2;"U$1,U$17";"#_GND#0";2;"";;;
3;"R10,R5,R7,R8";"0603";4;"2.2k";;;
4;"FRAME1";"CREATIVE_COMMONS";1;"FRAME-LETTER";;;
5;"U$16";"QWIIC_4MM";1;"";;;
6;"U3";"SOT23-5";1;"AP2127K-1.8V";;;
7;"C6";"0603";1;"100pF";;;
8;"U$10,U$21";"#GND_#0";2;"";;;
9;"U$15,U$26";"1#8V0";2;"";;;
10;"U$14,U$25";"#EN_#0";2;"";;;
11;"U$3,U$4,U$2,U$5";"STAND-OFF";4;"";;;
12;"U$8,U$20";"#_SCL#0";2;"";;;
13;"U$11,U$22";"#3V3_#0";2;"";;;
14;"U$13,U$24";"#SCL_#0";2;"";;;
15;"J4";"1X05_NO_SILK";1;"";;;
16;"U$7,U$19";"#_SDA#0";2;"";;;
17;"U4";"VSSOP_8PIN";1;"";;;
18;"U$12,U$23";"#SDA_#0";2;"";;;
19;"R1";"0603";1;"1k";;;
20;"U$6,U$18";"#_1V8#0";2;"";;;
21;"J2,J1";"JST04_1MM_RA";2;"QWIIC_RIGHT_ANGLE";;;
22;"R11";"0603";1;"200k";;;
23;"J5";"1X04_NO_SILK";1;"";;;
24;"D1";"LED-0603";1;"RED";;;
25;"U$9";"PWR0";1;"";;;
26;"EN0";"SMT-JUMPER_3_1-NC_TRACE_SILK";1;"JUMPER-SMT_3_1-NC_TRACE_SILK";;;
27;"U$30";"#LED#0";1;"";;;
28;"U$28";"QWIIC_1#8V_ADAPTER0";1;"";;;
29;"U$27";"#EN#0";1;"";;;
30;"JP1";"SMT-JUMPER_2_NC_TRACE_SILK";1;"JUMPER-SMT_2_NC_TRACE_SILK";;;
31;"U$29";"SPARKX-SMALL";1;"";;;

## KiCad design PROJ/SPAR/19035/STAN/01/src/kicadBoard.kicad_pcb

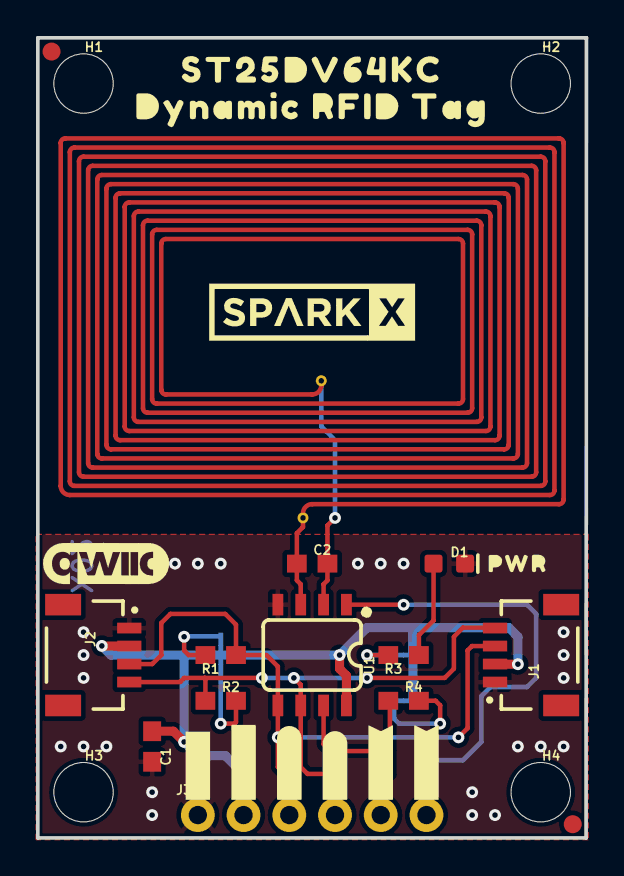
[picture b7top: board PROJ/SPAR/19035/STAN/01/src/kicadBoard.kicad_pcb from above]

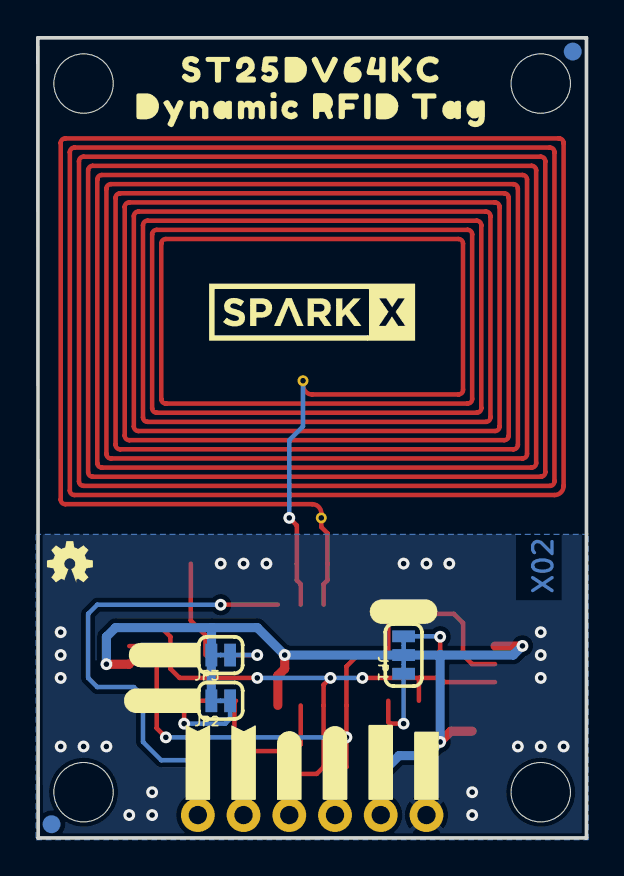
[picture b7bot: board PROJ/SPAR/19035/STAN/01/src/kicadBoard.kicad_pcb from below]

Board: 2 copper layers, 30.5 x 44.5 mm, 48 parts (18 on the bottom side), 13 nets.

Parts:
C1: 0.1uF; 0603
C2: 4.7pF; 0603
D1: RED; LED-0603
FD1, FD2, FD3, FD4: FIDUCIAL1X2; FIDUCIAL-1X2
FRAME1: FRAME-LETTERNO_PACKAGE; DUMMY
H1, H2, H3, H4: STAND-OFF
J1, J2: Qwiic; JST04_1MM_RA
J3: 1X06_NO_SILK
JP1: JUMPER-SMT_3_2-NC_TRACE_SILK; SMT-JUMPER_3_2-NC_TRACE_SILK
JP2, JP3: JUMPER-SMT_2_NC_TRACE_SILK; SMT-JUMPER_2_NC_TRACE_SILK
L1: PCB_4UH_INDUCTOR
LOGO1: OSHW-LOGOMINI; OSHW-LOGO-MINI
LOGO3: QWIIC_LOGO_7MM; QWIIC_7MM
R1, R2: 2.2k; 0603
R3: 1k; 0603
R4: 10k; 0603
U1: ST25DV64KC; SO08
U$1, U$2: SPARKX-LOGO5; SPARKX-LARGE
U$3, U$19: #3#3V#0
U$4, U$18: #GND#4
U$5, U$20: #SDA#5
U$6, U$21: #SCL#6
U$7, U$22: ##GPO##8
U$8, U$23: #VEH#7
U$9: PWR11
U$10, U$11: DYNAMIC_RFID_TAG0
U$13, U$24: ST25DV64KC5984
U$15: #I2C#11
U$16: ##GPO##9
U$17: #LED#10

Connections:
3.3V: C1.1, J1.2, J2.2, J3.2, JP1.2, JP2.2, JP3.2, U1.8
AC0: C2.2, L1.IN1, U1.2
AC1: C2.1, L1.IN2, U1.3
GND: C1.2, D1.C, J1.1, J2.1, J3.1, U1.4
unnamed: JP3.1, R3.2
unnamed: JP1.3, R1.2
unnamed: JP1.1, R2.2
unnamed: D1.A, R3.1
unnamed: JP2.1, R4.2
SCL: J1.4, J2.4, J3.4, R2.1, U1.6
SDA: J1.3, J2.3, J3.3, R1.1, U1.5
VEH: J3.6, U1.1
~GPO: J3.5, R4.1, U1.7

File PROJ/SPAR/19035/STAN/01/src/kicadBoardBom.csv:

"Id";"Designator";"Package";"Quantity";"Designation";"Supplier and ref";
1;"FD4,FD2,FD1,FD3";"FIDUCIAL-1X2";4;"FIDUCIAL1X2";;;
2;"U$5,U$20";"#SDA#5";2;"";;;
3;"U$10,U$11";"DYNAMIC_RFID_TAG0";2;"";;;
4;"R4";"0603";1;"10k";;;
5;"H4,H2,H1,H3";"STAND-OFF";4;"STAND-OFF";;;
6;"U$7,U$22";"##GPO##8";2;"";;;
7;"C1";"0603";1;"0.1uF";;;
8;"L1";"PCB_4UH_INDUCTOR";1;"PCB_4UH_INDUCTOR";;;
9;"R2,R1";"0603";2;"2.2k";;;
10;"J2,J1";"JST04_1MM_RA";2;"Qwiic";;;
11;"U$8,U$23";"#VEH#7";2;"";;;
12;"C2";"0603";1;"4.7pF";;;
13;"U$13,U$24";"ST25DV64KC5984";2;"";;;
14;"U$4,U$18";"#GND#4";2;"";;;
15;"U$9";"PWR11";1;"";;;
16;"U$1,U$2";"SPARKX-LARGE";2;"SPARKX-LOGO5";;;
17;"U1";"SO08";1;"ST25DV64KC";;;
18;"U$3,U$19";"#3#3V#0";2;"";;;
19;"LOGO3";"QWIIC_7MM";1;"QWIIC_LOGO_7MM";;;
20;"J3";"1X06_NO_SILK";1;"";;;
21;"U$6,U$21";"#SCL#6";2;"";;;
22;"R3";"0603";1;"1k";;;
23;"FRAME1";"DUMMY";1;"FRAME-LETTERNO_PACKAGE";;;
24;"D1";"LED-0603";1;"RED";;;
25;"JP1";"SMT-JUMPER_3_2-NC_TRACE_SILK";1;"JUMPER-SMT_3_2-NC_TRACE_SILK";;;
26;"U$17";"#LED#10";1;"";;;
27;"JP3,JP2";"SMT-JUMPER_2_NC_TRACE_SILK";2;"JUMPER-SMT_2_NC_TRACE_SILK";;;
28;"U$15";"#I2C#11";1;"";;;
29;"U$16";"##GPO##9";1;"";;;
30;"LOGO1";"OSHW-LOGO-MINI";1;"OSHW-LOGOMINI";;;

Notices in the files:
parts and their libraries:
RELEASED UNDER THE CREATIVE COMMONS ATTRIBUTION SHARE-ALIKE 4.0 LICENSE
HTTPS://CREATIVECOMMONS.ORG/LICENSES/BY-SA/4.0
